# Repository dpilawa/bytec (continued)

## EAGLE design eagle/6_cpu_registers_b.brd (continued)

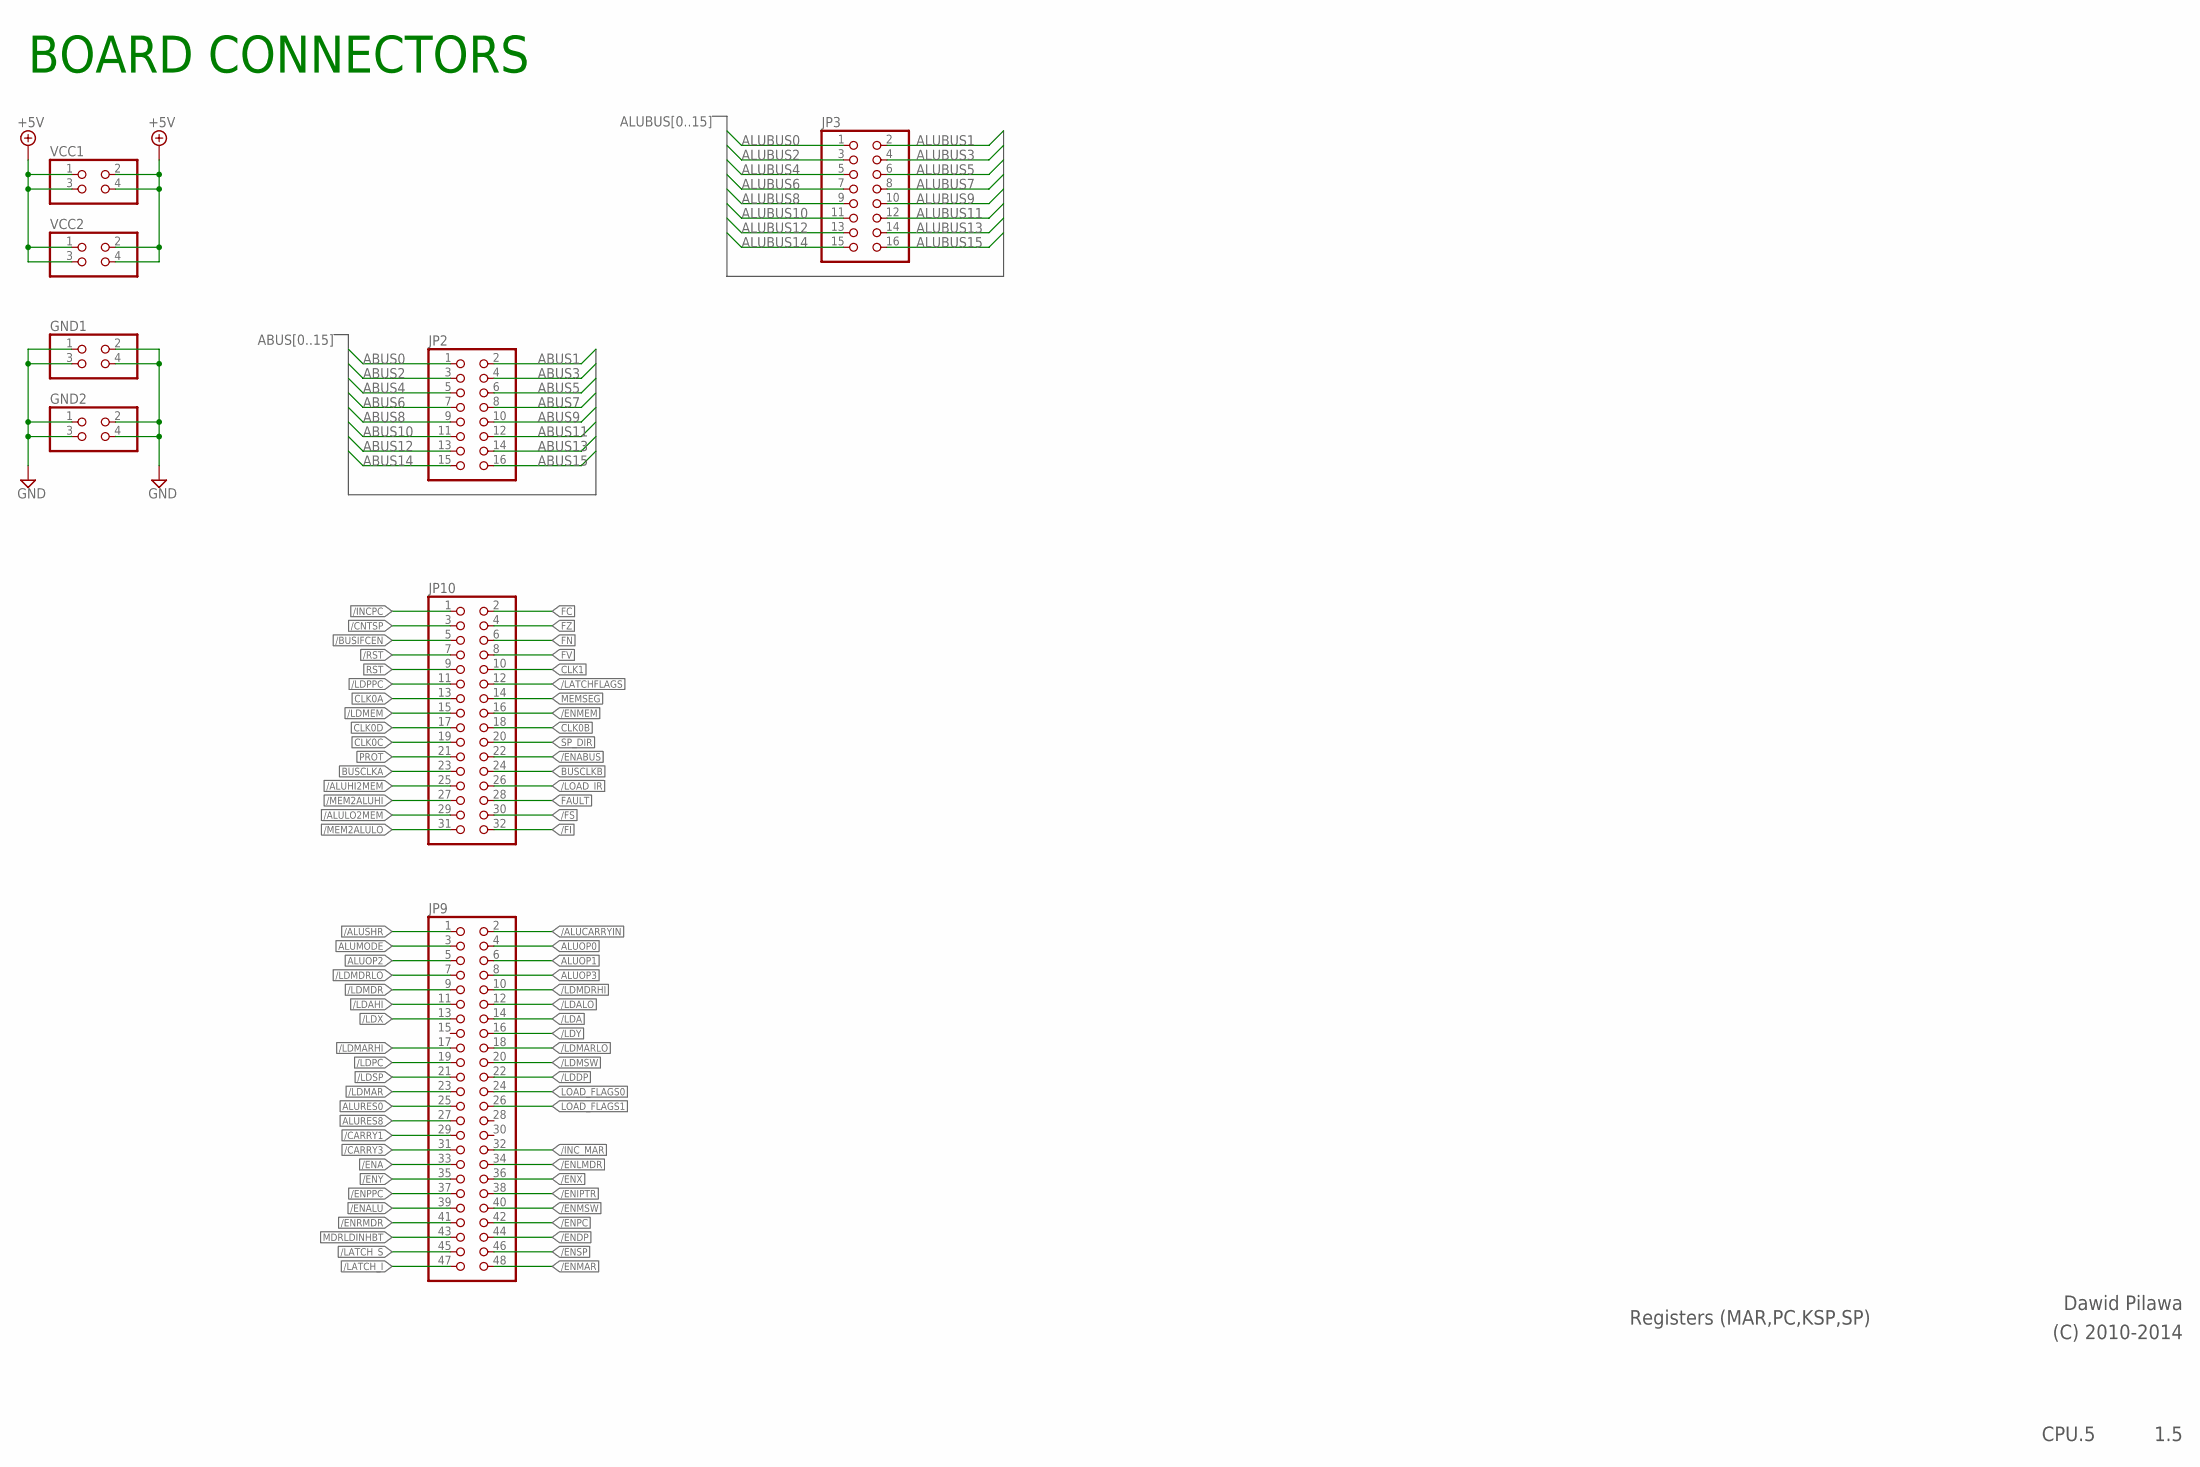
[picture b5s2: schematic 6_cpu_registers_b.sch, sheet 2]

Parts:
GND1, GND2: PINHD-2X2; 2X02
JP2, JP3: PINHD-2X8; 2X08
JP9: PINHD-2X24; 2X24
JP10: PINHD-2X16; 2X16
VCC1, VCC2: PINHD-2X2; 2X02

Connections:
+5V: VCC1.1, VCC1.2, VCC1.3, VCC1.4, VCC2.1, VCC2.2, VCC2.3, VCC2.4; also elsewhere on the board
/ALUCARRYIN: JP9.2
/ALUHI2MEM: JP10.25
/ALULO2MEM: JP10.29
/ALUSHR: JP9.1
/BUSIFCEN: JP10.5
/CARRY1: JP9.29
/CARRY3: JP9.31
/CNTSP: JP10.3; also elsewhere on the board
/ENA: JP9.33
/ENABUS: JP10.22
/ENALU: JP9.39
/ENDP: JP9.44
/ENIPTR: JP9.38
/ENLMDR: JP9.34
/ENMAR: JP9.48; also elsewhere on the board
/ENMEM: JP10.16
/ENMSW: JP9.40
/ENPC: JP9.42; also elsewhere on the board
/ENRMDR: JP9.41
/ENSP: JP9.46; also elsewhere on the board
/ENX: JP9.36
/ENY: JP9.35
/FI: JP10.32
/FS: JP10.30; also elsewhere on the board
/INCPC: JP10.1; also elsewhere on the board
/INC_MAR: JP9.32; also elsewhere on the board
/LATCHFLAGS: JP10.12
/LATCH_I: JP9.47
/LATCH_S: JP9.45
/LDA: JP9.14
/LDAHI: JP9.11
/LDALO: JP9.12
/LDDP: JP9.22
/LDMAR: JP9.23; also elsewhere on the board
/LDMARHI: JP9.17; also elsewhere on the board
/LDMARLO: JP9.18; also elsewhere on the board
/LDMDR: JP9.9
/LDMDRHI: JP9.10
/LDMDRLO: JP9.7
/LDMEM: JP10.15
/LDMSW: JP9.20
/LDPC: JP9.19; also elsewhere on the board
/LDSP: JP9.21; also elsewhere on the board
/LDX: JP9.13
/LDY: JP9.16
/LOAD_IR: JP10.26
/MEM2ALUHI: JP10.27
/MEM2ALULO: JP10.31
/RST: JP10.7; also elsewhere on the board
ABUS0: JP2.1; also elsewhere on the board
ABUS1: JP2.2; also elsewhere on the board
ABUS2: JP2.3; also elsewhere on the board
ABUS3: JP2.4; also elsewhere on the board
ABUS4: JP2.5; also elsewhere on the board
ABUS5: JP2.6; also elsewhere on the board
ABUS6: JP2.7; also elsewhere on the board
ABUS7: JP2.8; also elsewhere on the board
ABUS8: JP2.9; also elsewhere on the board
ABUS9: JP2.10; also elsewhere on the board
ABUS10: JP2.11; also elsewhere on the board
ABUS11: JP2.12; also elsewhere on the board
ABUS12: JP2.13; also elsewhere on the board
ABUS13: JP2.14; also elsewhere on the board
ABUS14: JP2.15; also elsewhere on the board
ABUS15: JP2.16; also elsewhere on the board
ALUBUS0: JP3.1; also elsewhere on the board
ALUBUS1: JP3.2; also elsewhere on the board
ALUBUS2: JP3.3; also elsewhere on the board
ALUBUS3: JP3.4; also elsewhere on the board
ALUBUS4: JP3.5; also elsewhere on the board
ALUBUS5: JP3.6; also elsewhere on the board
ALUBUS6: JP3.7; also elsewhere on the board
ALUBUS7: JP3.8; also elsewhere on the board
ALUBUS8: JP3.9; also elsewhere on the board
ALUBUS9: JP3.10; also elsewhere on the board
ALUBUS10: JP3.11; also elsewhere on the board
ALUBUS11: JP3.12; also elsewhere on the board
ALUBUS12: JP3.13; also elsewhere on the board
ALUBUS13: JP3.14; also elsewhere on the board
ALUBUS14: JP3.15; also elsewhere on the board
ALUBUS15: JP3.16; also elsewhere on the board
ALUMODE: JP9.3
ALUOP0: JP9.4
ALUOP1: JP9.6
ALUOP2: JP9.5
ALUOP3: JP9.8
ALURES0: JP9.25
ALURES8: JP9.27
BUSCLKA: JP10.23
BUSCLKB: JP10.24
CLK0A: JP10.13
CLK0B: JP10.18; also elsewhere on the board
CLK0C: JP10.19; also elsewhere on the board
CLK0D: JP10.17
CLK1: JP10.10
FAULT: JP10.28
FC: JP10.2
FN: JP10.6
FV: JP10.8
FZ: JP10.4
GND: GND1.1, GND1.2, GND1.3, GND1.4, GND2.1, GND2.2, GND2.3, GND2.4; also elsewhere on the board
LOAD_FLAGS0: JP9.24
LOAD_FLAGS1: JP9.26
MDRLDINHBT: JP9.43
MEMSEG: JP10.14
PROT: JP10.21
RST: JP10.9
SP_DIR: JP10.20; also elsewhere on the board

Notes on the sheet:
Registers (MAR,PC,KSP,SP)
Dawid Pilawa
(C) 2010-2014
CPU.5
1.5
BOARD CONNECTORS

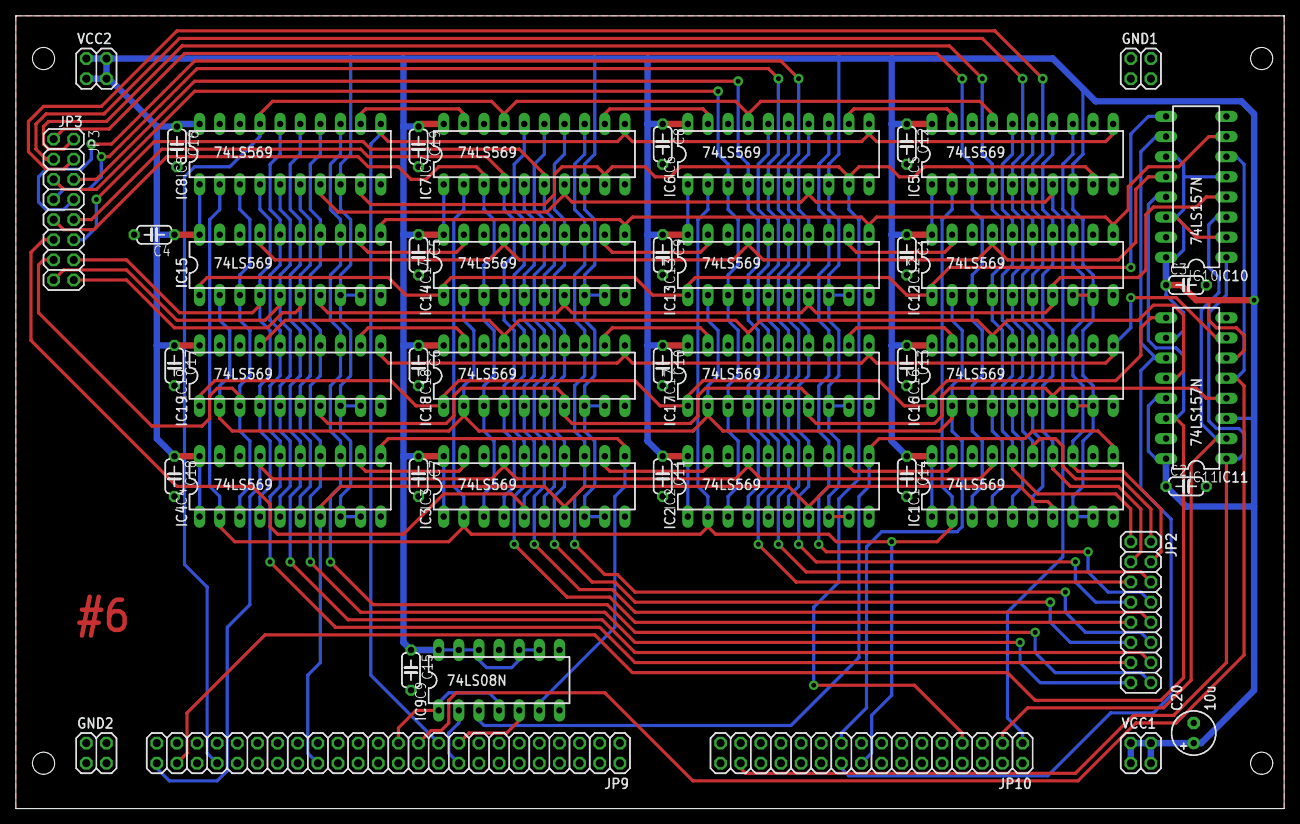
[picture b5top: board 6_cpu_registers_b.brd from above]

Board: 2 copper layers, 160.0 x 100.0 mm, 47 parts (0 on the bottom side), 72 nets.

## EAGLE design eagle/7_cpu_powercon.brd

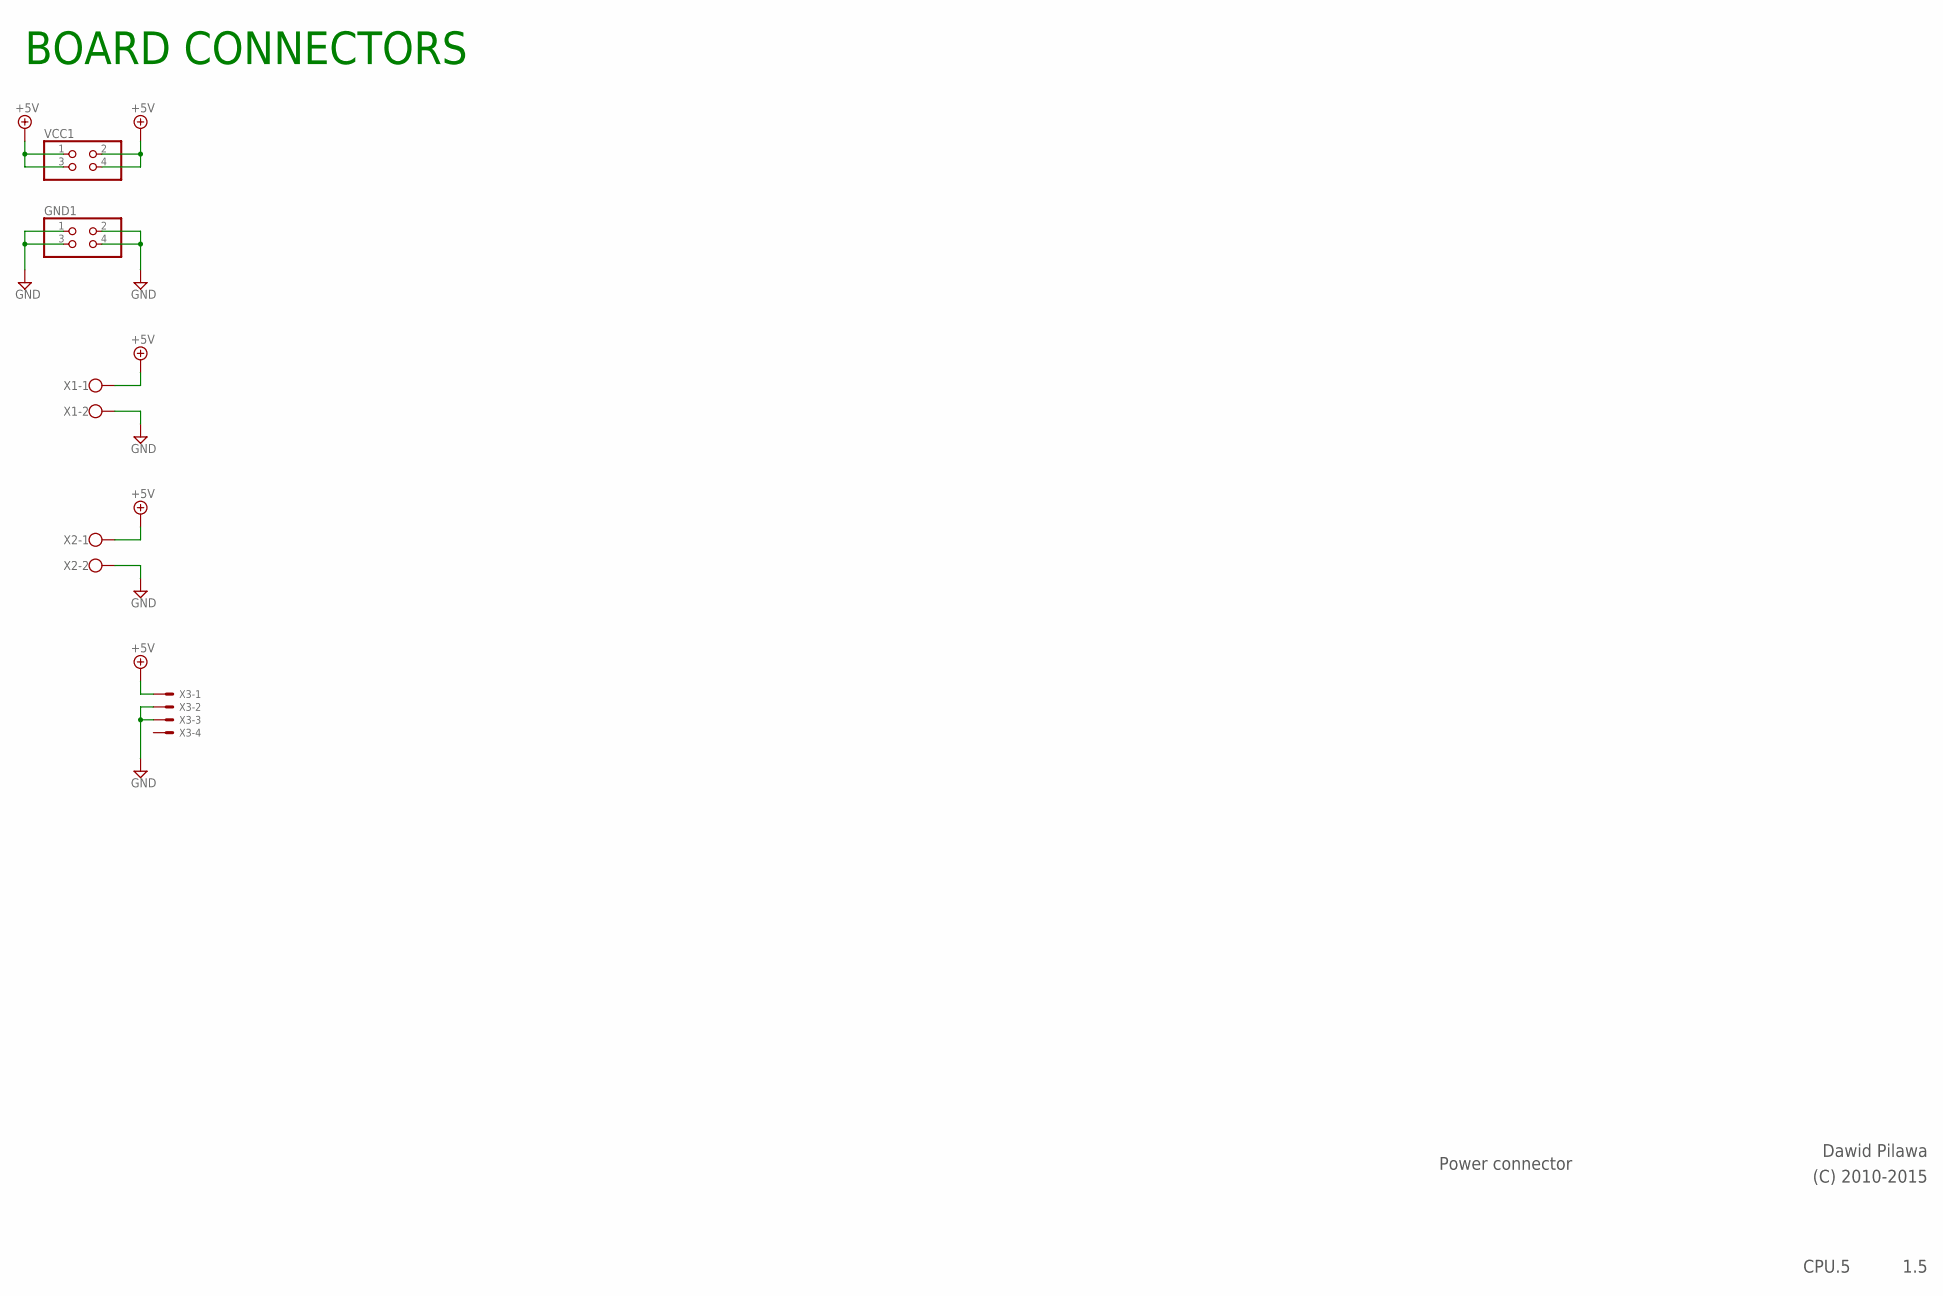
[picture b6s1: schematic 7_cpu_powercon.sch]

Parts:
GND1: PINHD-2X2; 2X02
VCC1: PINHD-2X2; 2X02
X1, X2: W237-102
X3: KK-156-4

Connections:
+5V: VCC1.1, VCC1.2, VCC1.3, VCC1.4, X1.1, X2.1, X3.1
GND: GND1.1, GND1.2, GND1.3, GND1.4, X1.2, X2.2, X3.2, X3.3

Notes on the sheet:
Power connector
Dawid Pilawa
(C) 2010-2015
CPU.5
1.5
BOARD CONNECTORS

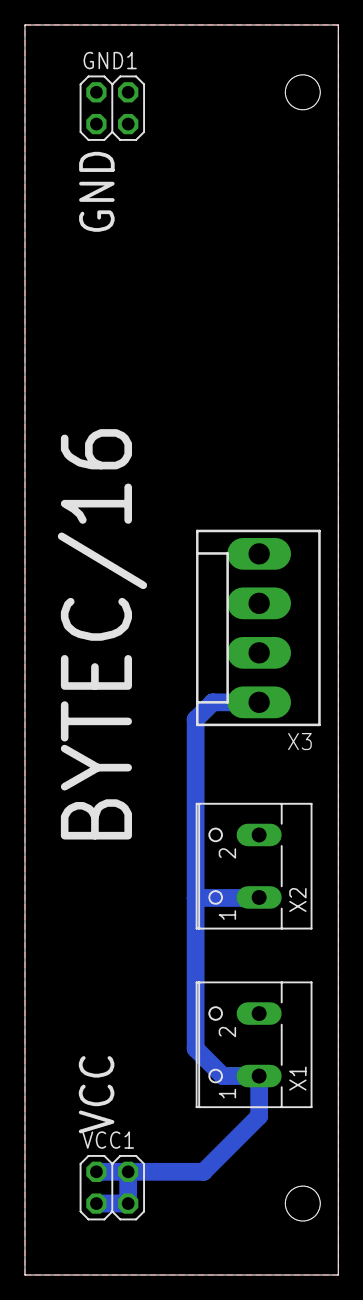
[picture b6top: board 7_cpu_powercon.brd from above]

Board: 2 copper layers, 25.1 x 100.0 mm, 5 parts (0 on the bottom side), 2 nets.
